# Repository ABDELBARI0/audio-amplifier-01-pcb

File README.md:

# Audio Amplifier PCB Design

A discrete-component audio amplifier PCB designed using **KiCad**. The project includes the electrical schematic, PCB layout, and a 3D visualization of the board and its component placement.

The circuit is designed to receive an audio signal through a 3.5 mm audio jack input and provide an amplified output through a separate output connector.

## Project Overview

The goal of this project is to design a printed circuit board (PCB) for an audio amplifier using discrete electronic components. The design process covers schematic capture, component placement, PCB routing, and 3D visualization.

**Project status:** Designed, not yet manufactured or tested.

## Features

- Audio signal input through a 3.5 mm audio jack.
- Amplified audio output through a separate connector.
- Discrete transistor-based amplifier circuitry.
- MOSFET output stage.
- PCB layout designed in KiCad.
- 3D visualization of component placement and board layout.
- Front and back copper layers, as configured in the PCB design.

## Design Previews

### 1. Electrical Schematic

The schematic illustrates the amplifier circuit, including its transistor stages, MOSFETs, resistors, capacitors, diode, power connections, and audio input/output interfaces.

### 2. PCB Layout and Component Placement

The PCB layout shows the copper routing, component footprints, connectors, and mounting holes.

### 3. 3D PCB View

The 3D render provides a visual representation of the board, including component placement, mounting holes, and overall layout.

*Replace the image paths above with the actual screenshot filenames committed to the repository.*

## Hardware Components

The design uses a combination of passive and active electronic components.

| Component | Purpose |
|---|---|
| Resistors | Biasing, current control, and circuit operation |
| Capacitors | Signal coupling, filtering, and power-supply decoupling |
| Diode | Protection or circuit biasing, depending on its role in the schematic |
| BC556 transistor | Small-signal transistor stage |
| BC546 transistors | Small-signal transistor stages |
| IRF540N MOSFET | N-channel MOSFET output stage |
| IRF9540N MOSFET | P-channel MOSFET output stage |
| Audio jack | Audio signal input |
| Screw terminal | Output connection |
| Mounting holes | Mechanical mounting of the PCB |

The component functions above describe their general roles. Actual operating conditions and circuit performance have not yet been verified through physical testing.

## Technical Details

| Parameter | Details |
|---|---|
| Project type | Audio amplifier PCB |
| Design software | KiCad |
| KiCad version | 10.0.7 |
| Design scope | Schematic, PCB layout, and 3D visualization |
| PCB copper | Front and back copper layers |
| Input interface | 3.5 mm audio jack |
| Output interface | Screw terminal |
| Main active components | BJTs and MOSFETs |
| Manufacturing status | Not manufactured |
| Testing status | Not tested |

The schematic shows positive and negative supply rails labeled `+36V` and `-36V`. These are schematic labels, not confirmation of a validated operating supply or tested performance.

Output power, frequency response, distortion, efficiency, and supported speaker impedance have not been specified.

## Repository Structure

The repository contains the KiCad design files and supporting project resources.

```text
audio-amplifier-01-pcb/
├── assistance/                  # Supporting screenshots or resources
├── .git/                        # Git repository metadata (local)
├── .history/                    # Local file history, if retained
├── fp-lib-table                 # Footprint library configuration
├── audio amplifier pcb.kicad_pcb # PCB layout
├── audio amplifier pcb.kicad_pro # KiCad project settings
├── audio amplifier pcb.kicad_sch # Electrical schematic
└── README.md                    # Project documentation
```

*The file tree is illustrative. Keep only filenames and folders that actually exist in your GitHub repository. The `.git` directory is normally local Git metadata and is not committed to GitHub.*

## Getting Started

To inspect the design locally:

1. Install [KiCad](https://www.kicad.org/).
2. Clone the repository:

   ```bash
   git clone https://github.com/ABDELBARI0/audio-amplifier-01-pcb.git
   ```

3. Open the KiCad project file (`.kicad_pro`).
4. Open the schematic editor to inspect the circuit.
5. Open the PCB editor to examine component placement and copper routing.
6. Use the 3D Viewer to inspect the board and component arrangement.

## Design Workflow

The project follows a typical PCB development workflow:

1. **Schematic capture:** Create the electrical circuit and establish component connections.
2. **Footprint assignment:** Associate schematic symbols with PCB footprints.
3. **PCB layout:** Arrange components and route electrical connections.
4. **3D visualization:** Review component placement and the overall board arrangement.
5. **Design verification:** Run electrical rule checks (ERC) and design rule checks (DRC) before fabrication.
6. **Future manufacturing and testing:** Fabricate the PCB, inspect the assembled circuit, and validate its electrical and audio performance.

The final verification, manufacturing, and testing stages remain future work.

## Future Improvements

- Complete electrical rule checking (ERC) and design rule checking (DRC).
- Verify component ratings and power-supply requirements.
- Generate Gerber and drill files for PCB fabrication.
- Manufacture and assemble the PCB.
- Perform safe initial power-up and electrical measurements.
- Test audio output quality, frequency response, and distortion.
- Document measured performance and any design revisions.

## Author

**GitHub:** [ABDELBARI0](https://github.com/ABDELBARI0)

**Project Repository:** [audio-amplifier-01-pcb](https://github.com/ABDELBARI0/audio-amplifier-01-pcb)

## License

No license has been specified yet. Add a license file if you intend to define how others may use, modify, or distribute this design.

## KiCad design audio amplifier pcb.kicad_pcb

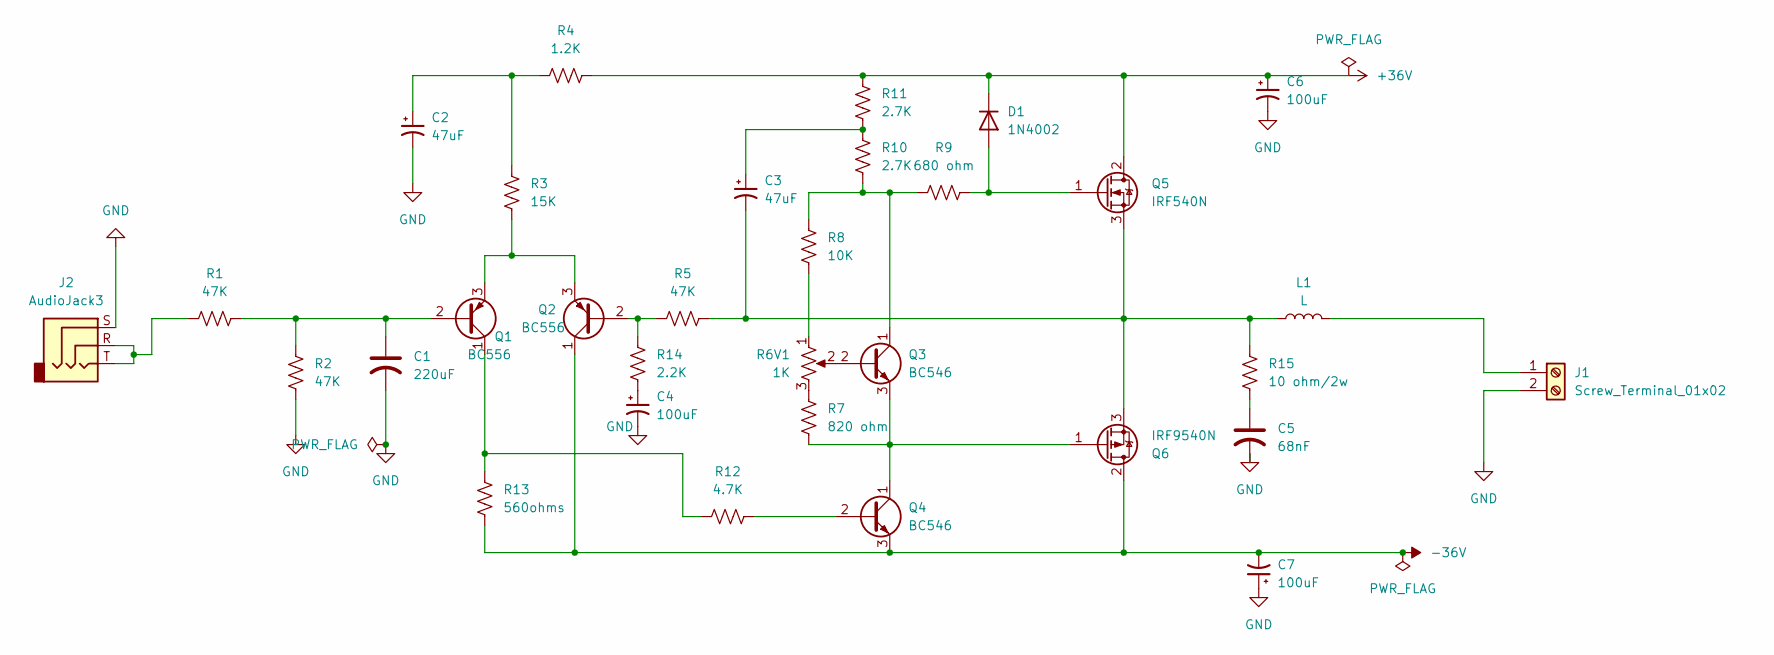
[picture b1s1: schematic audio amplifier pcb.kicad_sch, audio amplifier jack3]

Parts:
C1: 220uF; CP_Radial_D8.0mm_P5.00mm
C2, C3: 47uF; CP_Axial_L10.0mm_D6.0mm_P15.00mm_Horizontal
C4, C6, C7: 100uF; CP_Axial_L10.0mm_D6.0mm_P15.00mm_Horizontal
C5: 68nF; CP_Radial_D8.0mm_P5.00mm
D1: 1N4002; D_DO-41_SOD81_P10.16mm_Horizontal
J1: Screw_Terminal_01x02; TerminalBlock_MetzConnect_360410_1x01_Horizontal_ScrewM3.0
J2: AudioJack3; Jack_3.5mm_CUI_SJ-3523-SMT_Horizontal
L1: L; L_Neosid_SM-PIC0512H
Q1, Q2: BC556; TO-92_Inline
Q3, Q4: BC546; TO-92_Inline
Q5: IRF540N; TO-220-3_Vertical
Q6: IRF9540N; TO-220-3_Vertical
R1, R2, R5: 47K; R_Axial_DIN0411_L9.9mm_D3.6mm_P12.70mm_Horizontal
R3: 15K; R_Axial_DIN0411_L9.9mm_D3.6mm_P12.70mm_Horizontal
R4: 1.2K; R_Axial_DIN0411_L9.9mm_D3.6mm_P12.70mm_Horizontal
R6V1: 1K; Potentiometer_ACP_CA14-VSMD_Vertical
R7: 820 ohm; R_Axial_DIN0411_L9.9mm_D3.6mm_P12.70mm_Horizontal
R8: 10K; R_Axial_DIN0411_L9.9mm_D3.6mm_P12.70mm_Horizontal
R9: 680 ohm; R_Axial_DIN0411_L9.9mm_D3.6mm_P12.70mm_Horizontal
R10, R11: 2.7K; R_Axial_DIN0411_L9.9mm_D3.6mm_P12.70mm_Horizontal
R12: 4.7K; R_Axial_DIN0411_L9.9mm_D3.6mm_P12.70mm_Horizontal
R13: 560ohms; R_Axial_DIN0411_L9.9mm_D3.6mm_P12.70mm_Horizontal
R14: 2.2K; R_Axial_DIN0411_L9.9mm_D3.6mm_P12.70mm_Horizontal
R15: 10 ohm/2w; R_Axial_DIN0411_L9.9mm_D3.6mm_P12.70mm_Horizontal

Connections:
+36V: C6.1, D1.1 (K), Q5.2 (D), R4.2, R11.2
-36V: C7.2, Q2.1 (C), Q4.3 (E), Q6.2 (D), R13.1
GND: C1.2, C2.2, C4.2, C5.2, C6.2, C7.1, J1.2, J2.S, R2.2
unnamed: C2.1, R3.1, R4.1
unnamed: C3.1, R10.2, R11.1
unnamed: C4.1, R14.1
unnamed: C5.1, R15.2
unnamed: D1.2 (A), Q5.1 (G), R9.1
unnamed: J1.1 (Pin_1_1), L1.2
unnamed: J2.R, J2.T, R1.1
unnamed: C1.1, Q1.2 (B), R1.2, R2.1
unnamed: Q1.1 (C), R12.2, R13.2
unnamed: Q1.3 (E), Q2.3 (E), R3.2
unnamed: Q2.2 (B), R5.1, R14.2
unnamed: Q3.2 (B), R6V1.2
unnamed: Q3.1 (C), R8.2, R9.2, R10.1
unnamed: Q3.3 (E), Q4.1 (C), Q6.1 (G), R7.2
unnamed: Q4.2 (B), R12.1
unnamed: C3.2, L1.1, Q5.3 (S), Q6.3 (S), R5.2, R15.1
unnamed: R6V1.1, R8.1
unnamed: R6V1.3, R7.1

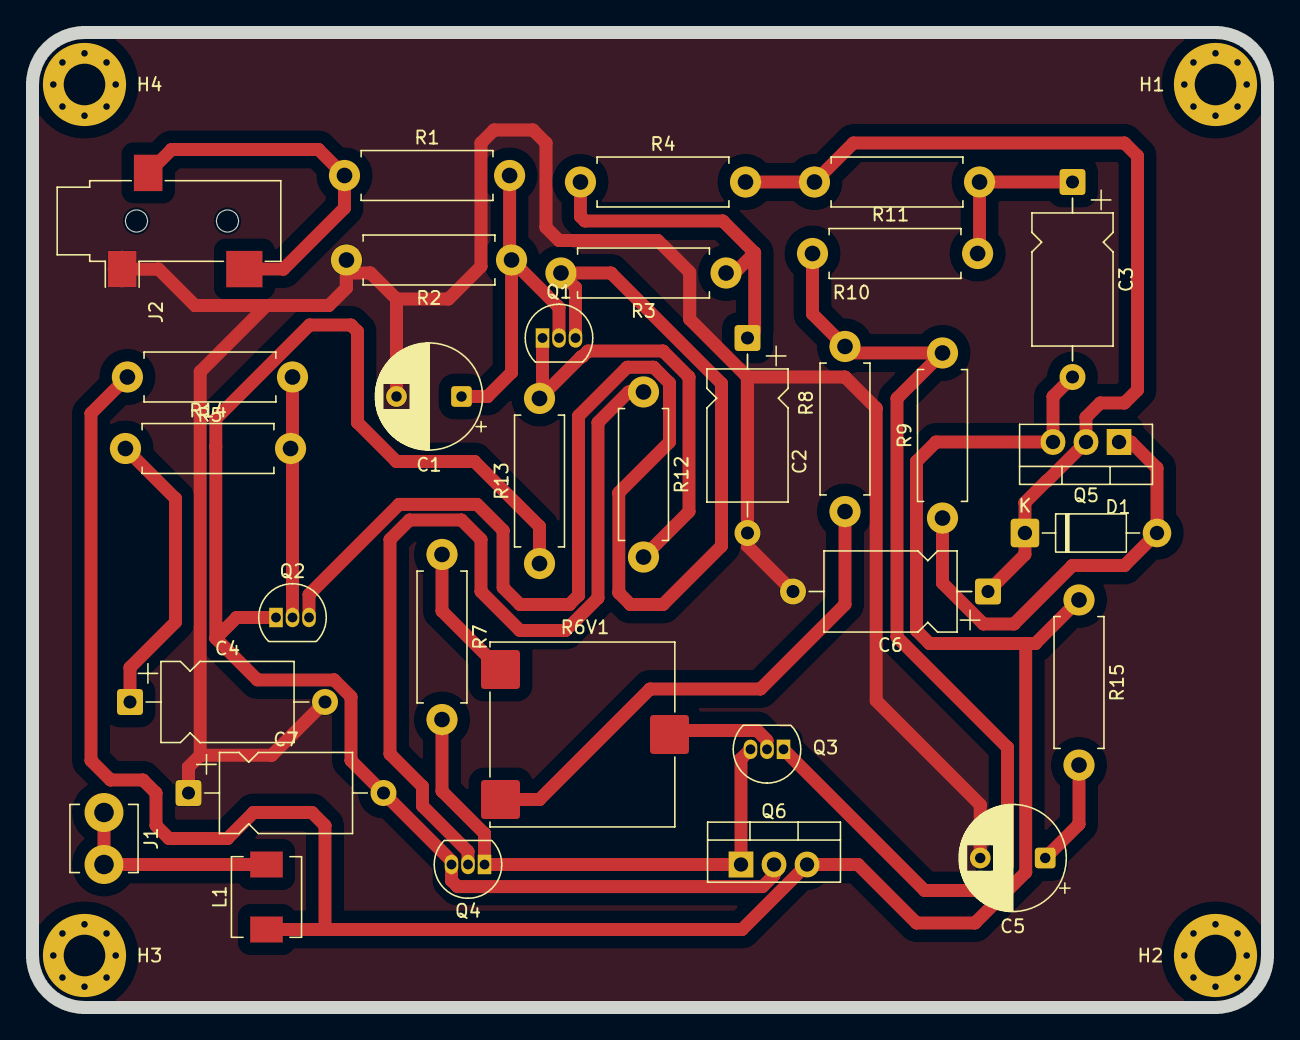
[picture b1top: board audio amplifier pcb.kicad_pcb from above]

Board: 2 copper layers, 95.0 x 75.0 mm, 36 parts (0 on the bottom side), 21 nets.

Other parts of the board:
H1, H2, H3, H4: MountingHole_3.2mm_M3_Pad_Via
